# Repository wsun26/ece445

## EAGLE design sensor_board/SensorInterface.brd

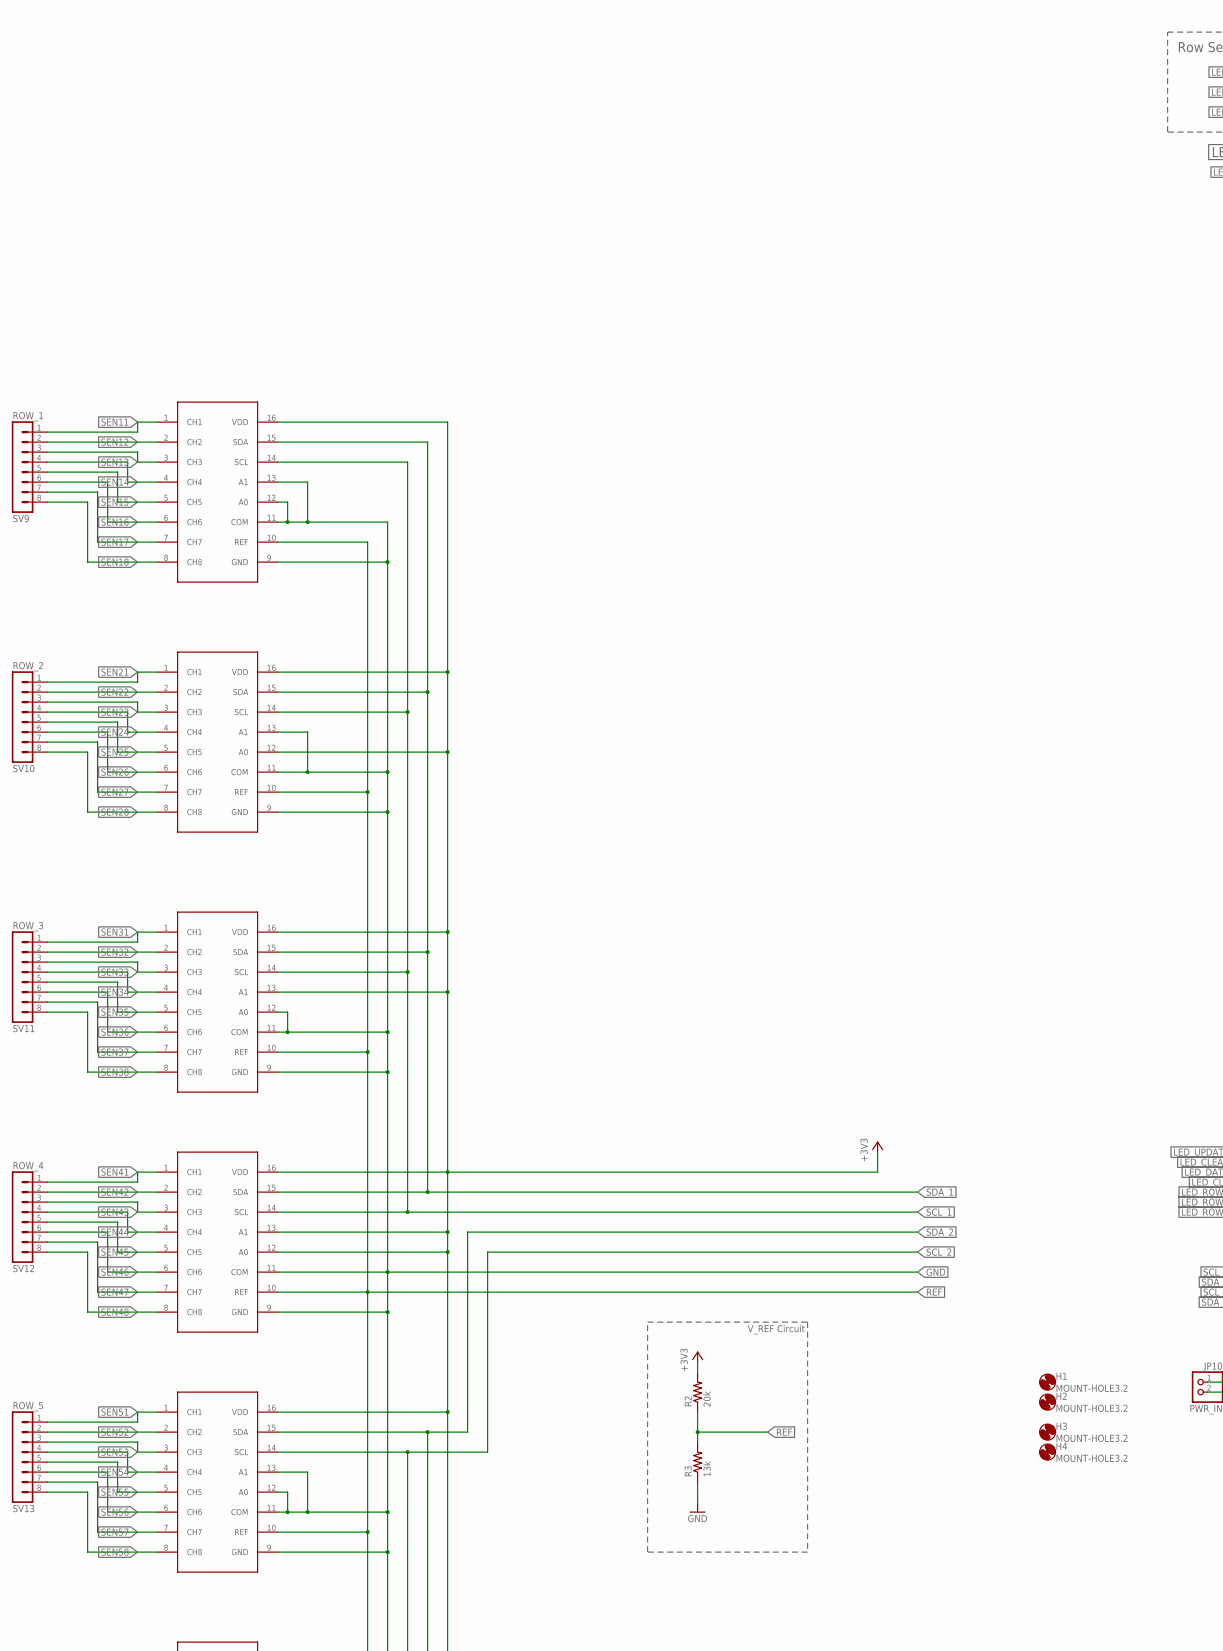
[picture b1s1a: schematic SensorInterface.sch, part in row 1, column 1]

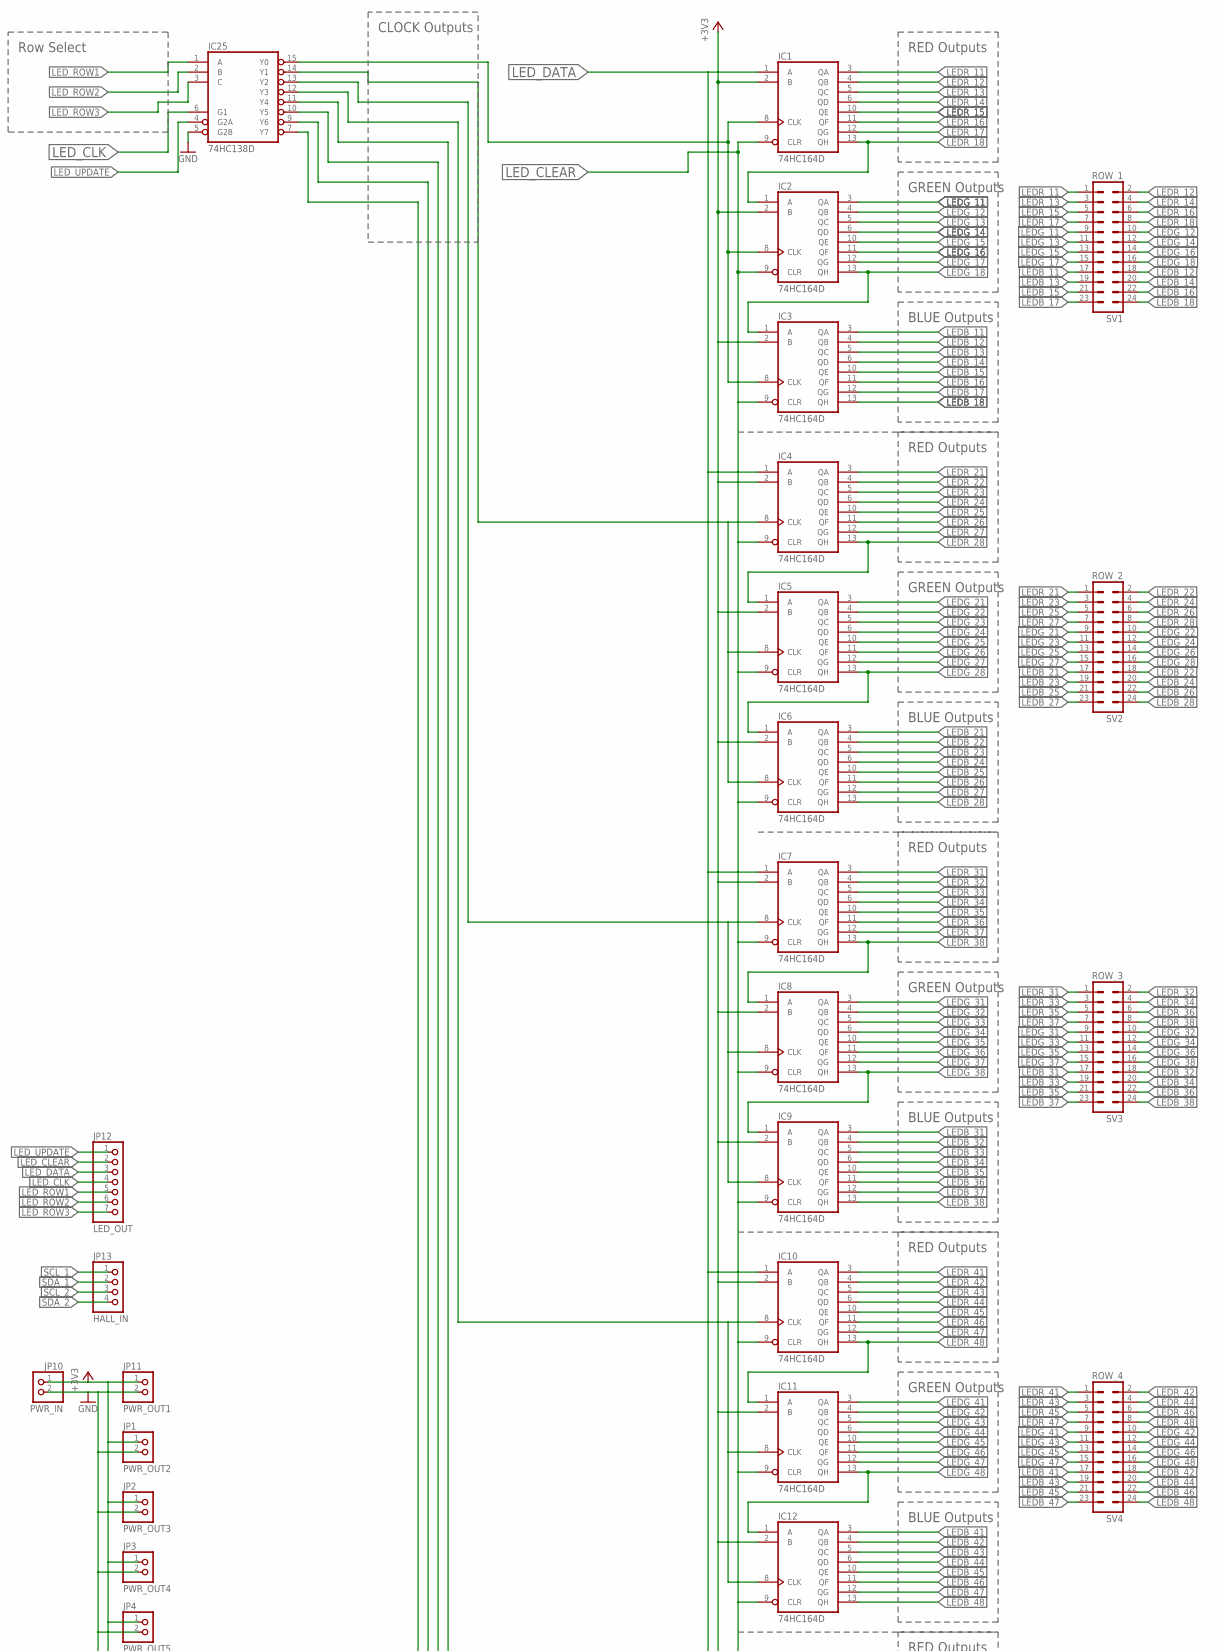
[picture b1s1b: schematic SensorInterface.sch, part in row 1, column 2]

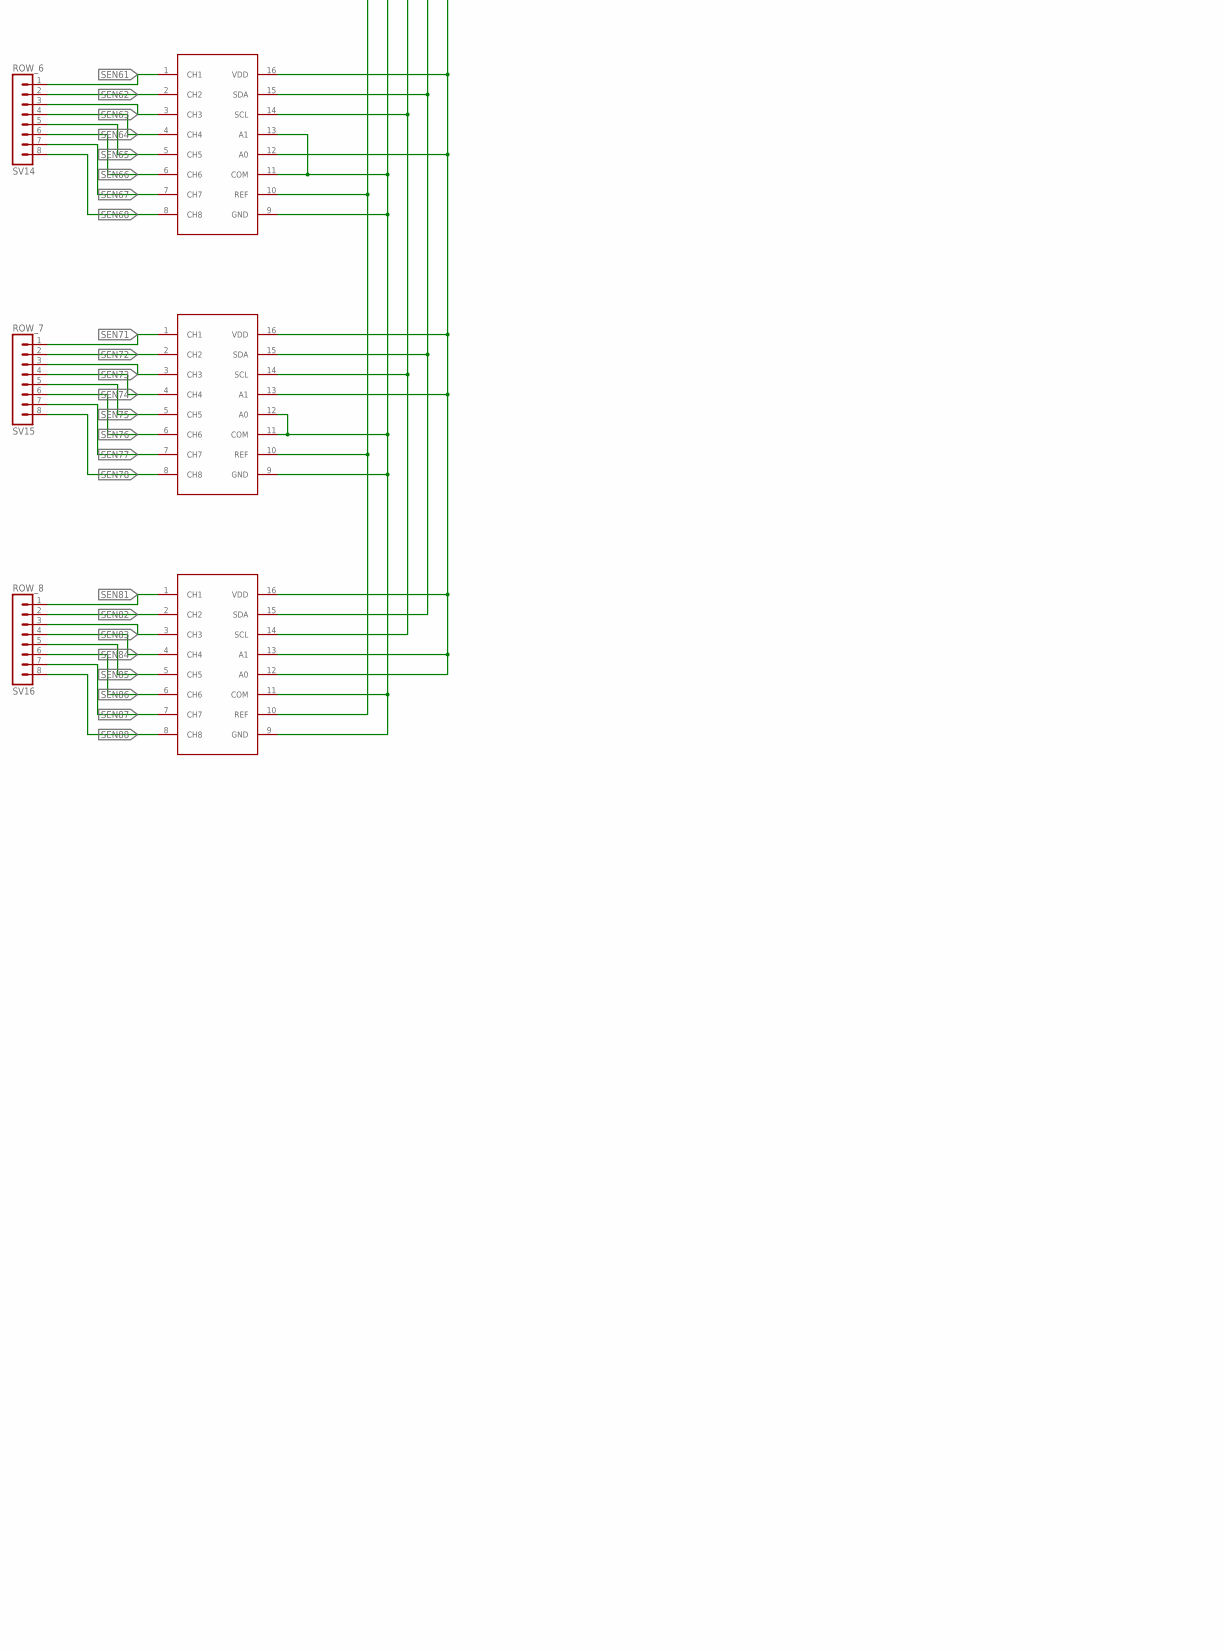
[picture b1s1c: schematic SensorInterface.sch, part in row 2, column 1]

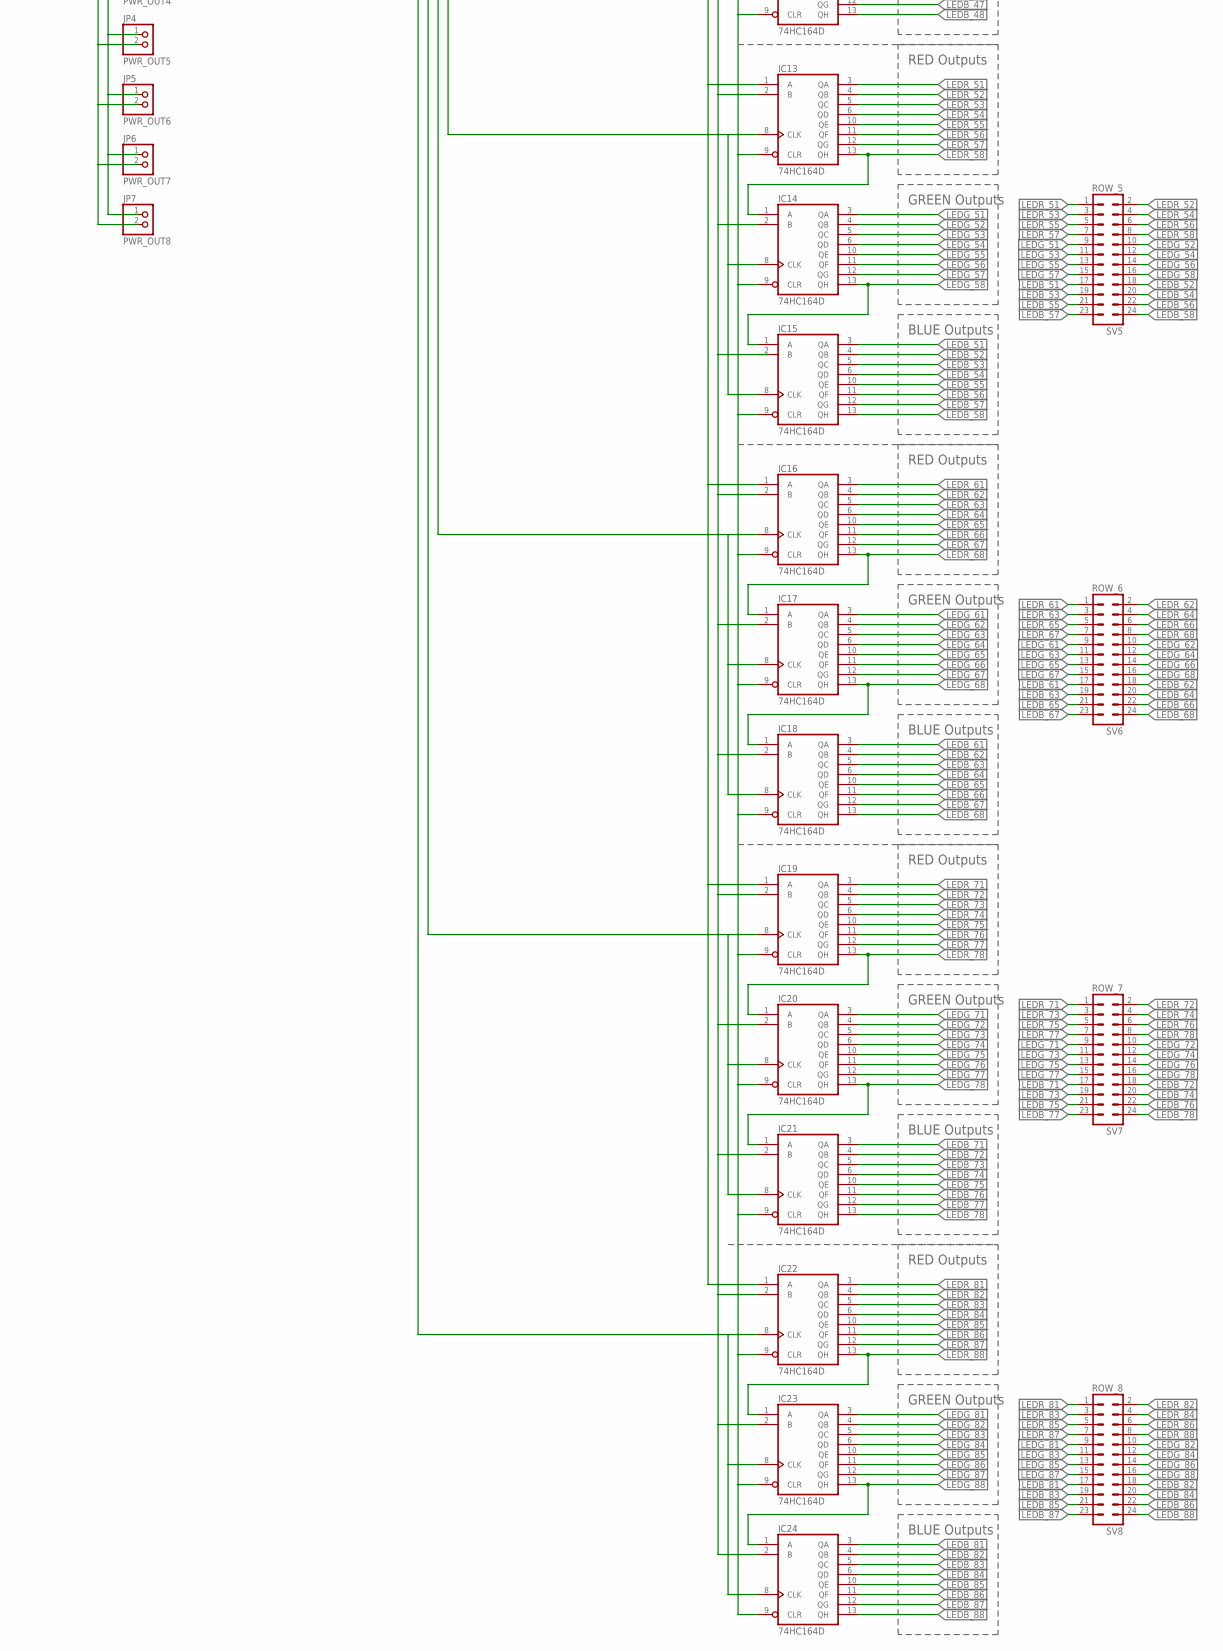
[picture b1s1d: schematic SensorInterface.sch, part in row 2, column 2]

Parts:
H1, H2, H3, H4: MOUNT-HOLE3.2; 3,2
IC1, IC2, IC3, IC4, IC5, IC6, IC7, IC8, IC9, IC10, IC11, IC12, IC13, IC14, IC15, IC16, IC17, IC18, IC19, IC20, IC21, IC22, IC23, IC24: 74HC164D; SO14
IC25: 74HC138D; SO16
JP1: PWR_OUT2; 1X02
JP2: PWR_OUT3; 1X02
JP3: PWR_OUT4; 1X02
JP4: PWR_OUT5; 1X02
JP5: PWR_OUT6; 1X02
JP6: PWR_OUT7; 1X02
JP7: PWR_OUT8; 1X02
JP10: PWR_IN; 1X02
JP11: PWR_OUT1; 1X02
JP12: LED_OUT; 1X07
JP13: HALL_IN; 1X04
R2: 20k; R0603
R3: 13k; R0603
SV1: ROW_1; MA12-2
SV2: ROW_2; MA12-2
SV3: ROW_3; MA12-2
SV4: ROW_4; MA12-2
SV5: ROW_5; MA12-2
SV6: ROW_6; MA12-2
SV7: ROW_7; MA12-2
SV8: ROW_8; MA12-2
SV9: ROW_1; MA08-1
SV10: ROW_2; MA08-1
SV11: ROW_3; MA08-1
SV12: ROW_4; MA08-1
SV13: ROW_5; MA08-1
SV14: ROW_6; MA08-1
SV15: ROW_7; MA08-1
SV16: ROW_8; MA08-1
U$1, U$2, U$3, U$4, U$5, U$6, U$7, U$8: NCD9830; TSSOP16

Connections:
+3V3: IC1.2 (B), IC2.2 (B), IC3.2 (B), IC4.2 (B), IC5.2 (B), IC6.2 (B), IC7.2 (B), IC8.2 (B), IC9.2 (B), IC10.2 (B), IC11.2 (B), IC12.2 (B), IC13.2 (B), IC14.2 (B), IC16.2 (B), IC17.2 (B), IC18.2 (B), IC19.2 (B), IC20.2 (B), IC21.2 (B), IC22.2 (B), IC23.2 (B), IC24.2 (B), JP1.1, JP2.1, JP3.1, JP4.1, JP5.1, JP6.1, JP7.1, JP10.1, JP11.1, R2.2, U$1.12 (A0), U$1.16 (VDD), U$2.13 (A1), U$2.16 (VDD), U$3.12 (A0), U$3.13 (A1), U$3.16 (VDD), U$4.16 (VDD), U$5.12 (A0), U$5.16 (VDD), U$6.13 (A1), U$6.16 (VDD), U$7.16 (VDD), U$8.12 (A0), U$8.13 (A1), U$8.16 (VDD)
CLK: IC19.8 (CLK), IC20.8 (CLK), IC21.8 (CLK), IC25.9 (Y6)
GND: IC1.7 (GND), IC2.7 (GND), IC3.7 (GND), IC4.7 (GND), IC5.7 (GND), IC6.7 (GND), IC7.7 (GND), IC8.7 (GND), IC9.7 (GND), IC10.7 (GND), IC11.7 (GND), IC12.7 (GND), IC13.7 (GND), IC14.7 (GND), IC15.7 (GND), IC16.7 (GND), IC17.7 (GND), IC18.7 (GND), IC19.7 (GND), IC20.7 (GND), IC21.7 (GND), IC22.7 (GND), IC23.7 (GND), IC24.7 (GND), IC25.5 (G2B), IC25.8 (GND), JP1.2, JP2.2, JP3.2, JP4.2, JP5.2, JP6.2, JP7.2, JP10.2, JP11.2, R3.1, U$1.9 (GND), U$1.11 (COM), U$1.13 (A1), U$2.9 (GND), U$2.11 (COM), U$2.12 (A0), U$3.9 (GND), U$3.11 (COM), U$4.9 (GND), U$4.11 (COM), U$4.12 (A0), U$4.13 (A1), U$5.9 (GND), U$5.11 (COM), U$5.13 (A1), U$6.9 (GND), U$6.11 (COM), U$6.12 (A0), U$7.9 (GND), U$7.11 (COM), U$7.12 (A0), U$7.13 (A1), U$8.9 (GND), U$8.11 (COM)
LEDB_11: IC3.3 (QA), SV1.17
LEDB_12: IC3.4 (QB), SV1.18
LEDB_13: IC3.5 (QC), SV1.19
LEDB_14: IC3.6 (QD), SV1.20
LEDB_15: IC3.10 (QE), SV1.21
LEDB_16: IC3.11 (QF), SV1.22
LEDB_17: IC3.12 (QG), SV1.23
LEDB_18: IC3.13 (QH), SV1.24
LEDB_21: IC6.3 (QA), SV2.17
LEDB_22: IC6.4 (QB), SV2.18
LEDB_23: IC6.5 (QC), SV2.19
LEDB_24: IC6.6 (QD), SV2.20
LEDB_25: IC6.10 (QE), SV2.21
LEDB_26: IC6.11 (QF), SV2.22
LEDB_27: IC6.12 (QG), SV2.23
LEDB_28: IC6.13 (QH), SV2.24
LEDB_31: IC9.3 (QA), SV3.17
LEDB_32: IC9.4 (QB), SV3.18
LEDB_33: IC9.5 (QC), SV3.19
LEDB_34: IC9.6 (QD), SV3.20
LEDB_35: IC9.10 (QE), SV3.21
LEDB_36: IC9.11 (QF), SV3.22
LEDB_37: IC9.12 (QG), SV3.23
LEDB_38: IC9.13 (QH), SV3.24
LEDB_41: IC12.3 (QA), SV4.17
LEDB_42: IC12.4 (QB), SV4.18
LEDB_43: IC12.5 (QC), SV4.19
LEDB_44: IC12.6 (QD), SV4.20
LEDB_45: IC12.10 (QE), SV4.21
LEDB_46: IC12.11 (QF), SV4.22
LEDB_47: IC12.12 (QG), SV4.23
LEDB_48: IC12.13 (QH), SV4.24
LEDB_51: IC15.3 (QA), SV5.17
LEDB_52: IC15.4 (QB), SV5.18
LEDB_53: IC15.5 (QC), SV5.19
LEDB_54: IC15.6 (QD), SV5.20
LEDB_55: IC15.10 (QE), SV5.21
LEDB_56: IC15.11 (QF), SV5.22
LEDB_57: IC15.12 (QG), SV5.23
LEDB_58: IC15.13 (QH), SV5.24
LEDB_61: IC18.3 (QA), SV6.17
LEDB_62: IC18.4 (QB), SV6.18
LEDB_63: IC18.5 (QC), SV6.19
LEDB_64: IC18.6 (QD), SV6.20
LEDB_65: IC18.10 (QE), SV6.21
LEDB_66: IC18.11 (QF), SV6.22
LEDB_67: IC18.12 (QG), SV6.23
LEDB_68: IC18.13 (QH), SV6.24
LEDB_71: IC21.3 (QA), SV7.17
LEDB_72: IC21.4 (QB), SV7.18
LEDB_73: IC21.5 (QC), SV7.19
LEDB_74: IC21.6 (QD), SV7.20
LEDB_75: IC21.10 (QE), SV7.21
LEDB_76: IC21.11 (QF), SV7.22
LEDB_77: IC21.12 (QG), SV7.23
LEDB_78: IC21.13 (QH), SV7.24
LEDB_81: IC24.3 (QA), SV8.17
LEDB_82: IC24.4 (QB), SV8.18
LEDB_83: IC24.5 (QC), SV8.19
LEDB_84: IC24.6 (QD), SV8.20
LEDB_85: IC24.10 (QE), SV8.21
LEDB_86: IC24.11 (QF), SV8.22
LEDB_87: IC24.12 (QG), SV8.23
LEDB_88: IC24.13 (QH), SV8.24
LEDG_11: IC2.3 (QA), SV1.9
LEDG_12: IC2.4 (QB), SV1.10
LEDG_13: IC2.5 (QC), SV1.11
LEDG_14: IC2.6 (QD), SV1.12
LEDG_15: IC2.10 (QE), SV1.13
LEDG_16: IC2.11 (QF), SV1.14
LEDG_17: IC2.12 (QG), SV1.15
LEDG_18: IC2.13 (QH), IC3.1 (A), SV1.16
LEDG_21: IC5.3 (QA), SV2.9
LEDG_22: IC5.4 (QB), SV2.10
LEDG_23: IC5.5 (QC), SV2.11
LEDG_24: IC5.6 (QD), SV2.12
LEDG_25: IC5.10 (QE), SV2.13
LEDG_26: IC5.11 (QF), SV2.14
LEDG_27: IC5.12 (QG), SV2.15
LEDG_28: IC5.13 (QH), IC6.1 (A), SV2.16
LEDG_31: IC8.3 (QA), SV3.9
LEDG_32: IC8.4 (QB), SV3.10
LEDG_33: IC8.5 (QC), SV3.11
LEDG_34: IC8.6 (QD), SV3.12
LEDG_35: IC8.10 (QE), SV3.13
LEDG_36: IC8.11 (QF), SV3.14
LEDG_37: IC8.12 (QG), SV3.15
LEDG_38: IC8.13 (QH), IC9.1 (A), SV3.16
LEDG_41: IC11.3 (QA), SV4.9
LEDG_42: IC11.4 (QB), SV4.10
LEDG_43: IC11.5 (QC), SV4.11
LEDG_44: IC11.6 (QD), SV4.12
LEDG_45: IC11.10 (QE), SV4.13
LEDG_46: IC11.11 (QF), SV4.14
LEDG_47: IC11.12 (QG), SV4.15
LEDG_48: IC11.13 (QH), IC12.1 (A), SV4.16
LEDG_51: IC14.3 (QA), SV5.9
LEDG_52: IC14.4 (QB), SV5.10
LEDG_53: IC14.5 (QC), SV5.11
LEDG_54: IC14.6 (QD), SV5.12
LEDG_55: IC14.10 (QE), SV5.13
LEDG_56: IC14.11 (QF), SV5.14
LEDG_57: IC14.12 (QG), SV5.15
LEDG_58: IC14.13 (QH), IC15.1 (A), SV5.16
LEDG_61: IC17.3 (QA), SV6.9
LEDG_62: IC17.4 (QB), SV6.10
LEDG_63: IC17.5 (QC), SV6.11
LEDG_64: IC17.6 (QD), SV6.12
LEDG_65: IC17.10 (QE), SV6.13
LEDG_66: IC17.11 (QF), SV6.14
LEDG_67: IC17.12 (QG), SV6.15
LEDG_68: IC17.13 (QH), IC18.1 (A), SV6.16
LEDG_71: IC20.3 (QA), SV7.9
LEDG_72: IC20.4 (QB), SV7.10
LEDG_73: IC20.5 (QC), SV7.11
LEDG_74: IC20.6 (QD), SV7.12
LEDG_75: IC20.10 (QE), SV7.13
LEDG_76: IC20.11 (QF), SV7.14
LEDG_77: IC20.12 (QG), SV7.15
LEDG_78: IC20.13 (QH), IC21.1 (A), SV7.16
LEDG_81: IC23.3 (QA), SV8.9
LEDG_82: IC23.4 (QB), SV8.10
LEDG_83: IC23.5 (QC), SV8.11
LEDG_84: IC23.6 (QD), SV8.12
LEDG_85: IC23.10 (QE), SV8.13
LEDG_86: IC23.11 (QF), SV8.14
LEDG_87: IC23.12 (QG), SV8.15
LEDG_88: IC23.13 (QH), IC24.1 (A), SV8.16
LEDR_11: IC1.3 (QA), SV1.1
LEDR_12: IC1.4 (QB), SV1.2
LEDR_13: IC1.5 (QC), SV1.3
LEDR_14: IC1.6 (QD), SV1.4
LEDR_15: IC1.10 (QE), SV1.5
LEDR_16: IC1.11 (QF), SV1.6
LEDR_17: IC1.12 (QG), SV1.7
LEDR_18: IC1.13 (QH), IC2.1 (A), SV1.8
LEDR_21: IC4.3 (QA), SV2.1
LEDR_22: IC4.4 (QB), SV2.2
LEDR_23: IC4.5 (QC), SV2.3
LEDR_24: IC4.6 (QD), SV2.4
LEDR_25: IC4.10 (QE), SV2.5
LEDR_26: IC4.11 (QF), SV2.6
LEDR_27: IC4.12 (QG), SV2.7
LEDR_28: IC4.13 (QH), IC5.1 (A), SV2.8
LEDR_31: IC7.3 (QA), SV3.1
LEDR_32: IC7.4 (QB), SV3.2
LEDR_33: IC7.5 (QC), SV3.3
LEDR_34: IC7.6 (QD), SV3.4
LEDR_35: IC7.10 (QE), SV3.5
LEDR_36: IC7.11 (QF), SV3.6
LEDR_37: IC7.12 (QG), SV3.7
LEDR_38: IC7.13 (QH), IC8.1 (A), SV3.8
LEDR_41: IC10.3 (QA), SV4.1
LEDR_42: IC10.4 (QB), SV4.2
LEDR_43: IC10.5 (QC), SV4.3
LEDR_44: IC10.6 (QD), SV4.4
LEDR_45: IC10.10 (QE), SV4.5
LEDR_46: IC10.11 (QF), SV4.6
LEDR_47: IC10.12 (QG), SV4.7
LEDR_48: IC10.13 (QH), IC11.1 (A), SV4.8
LEDR_51: IC13.3 (QA), SV5.1
LEDR_52: IC13.4 (QB), SV5.2
LEDR_53: IC13.5 (QC), SV5.3
LEDR_54: IC13.6 (QD), SV5.4
LEDR_55: IC13.10 (QE), SV5.5
LEDR_56: IC13.11 (QF), SV5.6
LEDR_57: IC13.12 (QG), SV5.7
LEDR_58: IC13.13 (QH), IC14.1 (A), SV5.8
LEDR_61: IC16.3 (QA), SV6.1
LEDR_62: IC16.4 (QB), SV6.2
LEDR_63: IC16.5 (QC), SV6.3
LEDR_64: IC16.6 (QD), SV6.4
LEDR_65: IC16.10 (QE), SV6.5
LEDR_66: IC16.11 (QF), SV6.6
LEDR_67: IC16.12 (QG), SV6.7
LEDR_68: IC16.13 (QH), IC17.1 (A), SV6.8
LEDR_71: IC19.3 (QA), SV7.1
LEDR_72: IC19.4 (QB), SV7.2
LEDR_73: IC19.5 (QC), SV7.3
LEDR_74: IC19.6 (QD), SV7.4
LEDR_75: IC19.10 (QE), SV7.5
LEDR_76: IC19.11 (QF), SV7.6
LEDR_77: IC19.12 (QG), SV7.7
LEDR_78: IC19.13 (QH), IC20.1 (A), SV7.8
LEDR_81: IC22.3 (QA), SV8.1
LEDR_82: IC22.4 (QB), SV8.2
LEDR_83: IC22.5 (QC), SV8.3
LEDR_84: IC22.6 (QD), SV8.4
LEDR_85: IC22.10 (QE), SV8.5
LEDR_86: IC22.11 (QF), SV8.6
LEDR_87: IC22.12 (QG), SV8.7
LEDR_88: IC22.13 (QH), IC23.1 (A), SV8.8
LED_CLEAR: IC1.9 (CLR), IC2.9 (CLR), IC3.9 (CLR), IC4.9 (CLR), IC5.9 (CLR), IC6.9 (CLR), IC7.9 (CLR), IC8.9 (CLR), IC9.9 (CLR), IC10.9 (CLR), IC11.9 (CLR), IC12.9 (CLR), IC13.9 (CLR), IC14.9 (CLR), IC15.9 (CLR), IC16.9 (CLR), IC17.9 (CLR), IC18.9 (CLR), IC19.9 (CLR), IC20.9 (CLR), IC21.9 (CLR), IC22.9 (CLR), IC23.9 (CLR), IC24.9 (CLR), JP12.2
LED_CLK: IC25.6 (G1), JP12.4
LED_DATA: IC1.1 (A), IC4.1 (A), IC7.1 (A), IC10.1 (A), IC13.1 (A), IC16.1 (A), IC19.1 (A), IC22.1 (A), JP12.3
LED_ROW1: IC25.1 (A), JP12.5
LED_ROW2: IC25.2 (B), JP12.6
LED_ROW3: IC25.3 (C), JP12.7
LED_UPDATE: IC25.4 (G2A), JP12.1
unnamed: IC1.8 (CLK), IC2.8 (CLK), IC3.8 (CLK), IC25.15 (Y0)
unnamed: IC4.8 (CLK), IC5.8 (CLK), IC6.8 (CLK), IC25.14 (Y1)
unnamed: IC7.8 (CLK), IC8.8 (CLK), IC9.8 (CLK), IC25.13 (Y2)
unnamed: IC10.8 (CLK), IC11.8 (CLK), IC12.8 (CLK), IC25.12 (Y3)
unnamed: IC13.8 (CLK), IC14.8 (CLK), IC15.8 (CLK), IC25.11 (Y4)
unnamed: IC16.8 (CLK), IC17.8 (CLK), IC18.8 (CLK), IC25.10 (Y5)
unnamed: IC22.8 (CLK), IC23.8 (CLK), IC24.8 (CLK), IC25.7 (Y7)
REF: R2.1, R3.2, U$1.10 (REF), U$2.10 (REF), U$3.10 (REF), U$4.10 (REF), U$5.10 (REF), U$6.10 (REF), U$7.10 (REF), U$8.10 (REF)
SCL_1: JP13.1, U$1.14 (SCL), U$2.14 (SCL), U$3.14 (SCL), U$7.14 (SCL)
SCL_2: JP13.3, U$4.14 (SCL), U$5.14 (SCL), U$6.14 (SCL), U$8.14 (SCL)
SDA_1: JP13.2, U$1.15 (SDA), U$2.15 (SDA), U$3.15 (SDA), U$7.15 (SDA)
SDA_2: JP13.4, U$4.15 (SDA), U$5.15 (SDA), U$6.15 (SDA), U$8.15 (SDA)
SEN11: SV9.1, U$7.1 (CH1)
SEN12: SV9.2, U$7.2 (CH2)
SEN13: SV9.3, U$7.3 (CH3)
SEN14: SV9.4, U$7.4 (CH4)
SEN15: SV9.5, U$7.5 (CH5)
SEN16: SV9.6, U$7.6 (CH6)
SEN17: SV9.7, U$7.7 (CH7)
SEN18: SV9.8, U$7.8 (CH8)
SEN21: SV10.1
SEN22: SV10.2
SEN23: SV10.3
SEN24: SV10.4
SEN25: SV10.5
SEN26: SV10.6
SEN27: SV10.7
SEN28: SV10.8
SEN31: SV11.1
SEN32: SV11.2
SEN33: SV11.3
SEN34: SV11.4
SEN35: SV11.5
SEN36: SV11.6
SEN37: SV11.7
SEN38: SV11.8
SEN41: SV12.1
SEN42: SV12.2
SEN43: SV12.3
SEN44: SV12.4
SEN45: SV12.5
SEN46: SV12.6
SEN47: SV12.7
SEN48: SV12.8
SEN51: SV13.1
SEN52: SV13.2
SEN53: SV13.3
SEN54: SV13.4
SEN55: SV13.5
SEN56: SV13.6
SEN57: SV13.7
SEN58: SV13.8
SEN61: SV14.1
SEN62: SV14.2
SEN63: SV14.3
SEN64: SV14.4
SEN65: SV14.5
SEN66: SV14.6
SEN67: SV14.7
SEN68: SV14.8
SEN71: SV15.1
SEN72: SV15.2
SEN73: SV15.3
SEN74: SV15.4
SEN75: SV15.5
SEN76: SV15.6
SEN77: SV15.7
SEN78: SV15.8
SEN81: SV16.1
SEN82: SV16.2
SEN83: SV16.3
SEN84: SV16.4
SEN85: SV16.5
SEN86: SV16.6
SEN87: SV16.7
SEN88: SV16.8
VCC: IC1.14 (VCC), IC2.14 (VCC), IC3.14 (VCC), IC4.14 (VCC), IC5.14 (VCC), IC6.14 (VCC), IC7.14 (VCC), IC8.14 (VCC), IC9.14 (VCC), IC10.14 (VCC), IC11.14 (VCC), IC12.14 (VCC), IC13.14 (VCC), IC14.14 (VCC), IC15.14 (VCC), IC16.14 (VCC), IC17.14 (VCC), IC18.14 (VCC), IC19.14 (VCC), IC20.14 (VCC), IC21.14 (VCC), IC22.14 (VCC), IC23.14 (VCC), IC24.14 (VCC), IC25.16 (VCC)

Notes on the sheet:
V_REF Circuit
RED Outputs
GREEN Outputs
BLUE Outputs
CLOCK Outputs
Row Select

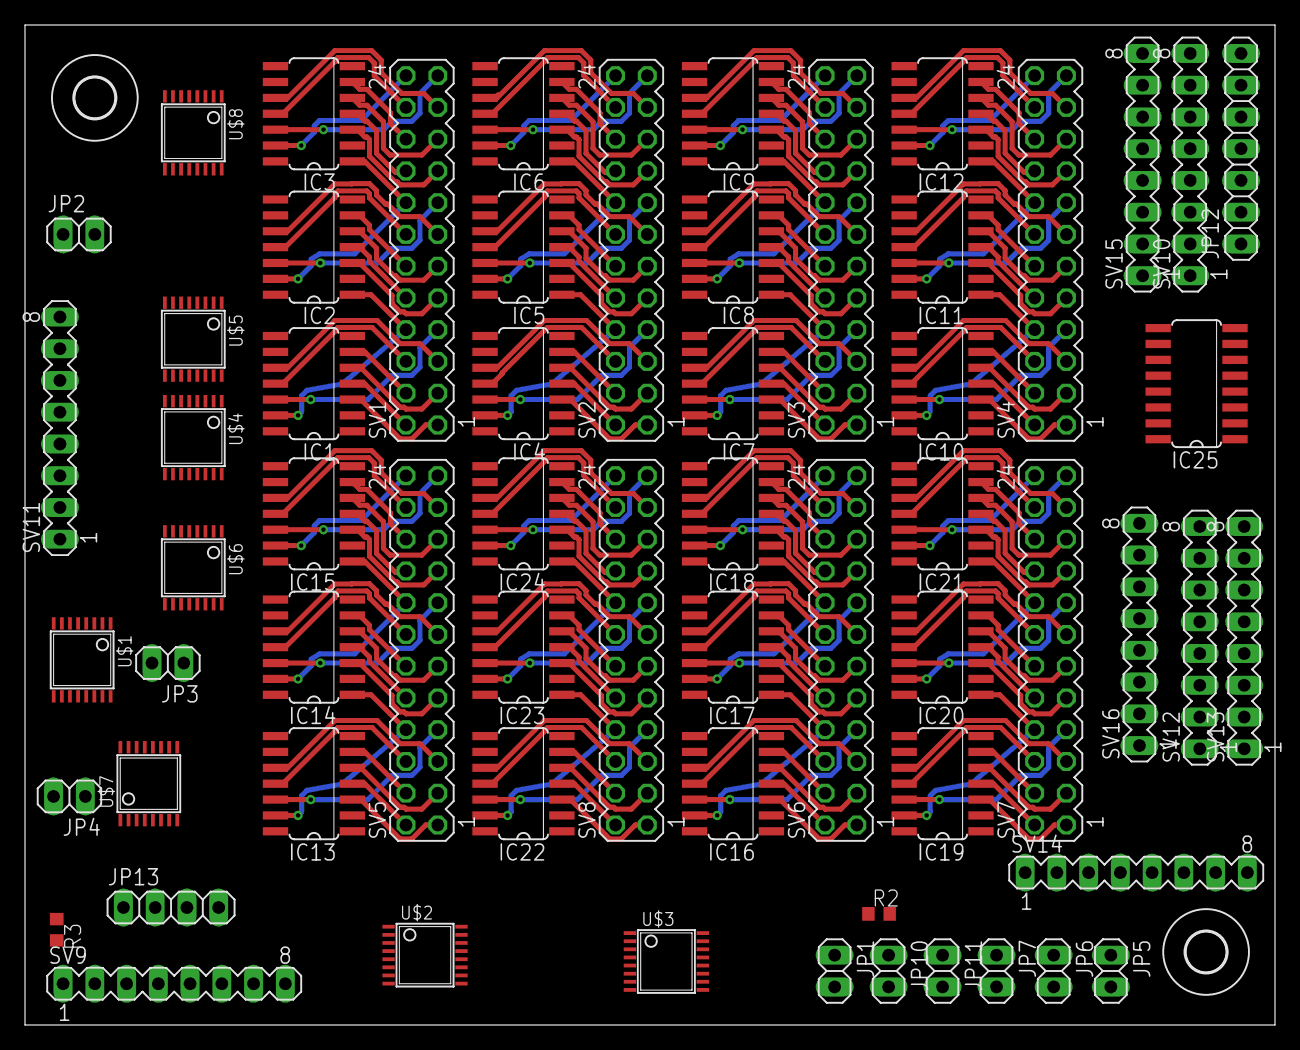
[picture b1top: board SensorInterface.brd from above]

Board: 2 copper layers, 100.0 x 80.0 mm, 66 parts (0 on the bottom side), 223 nets.

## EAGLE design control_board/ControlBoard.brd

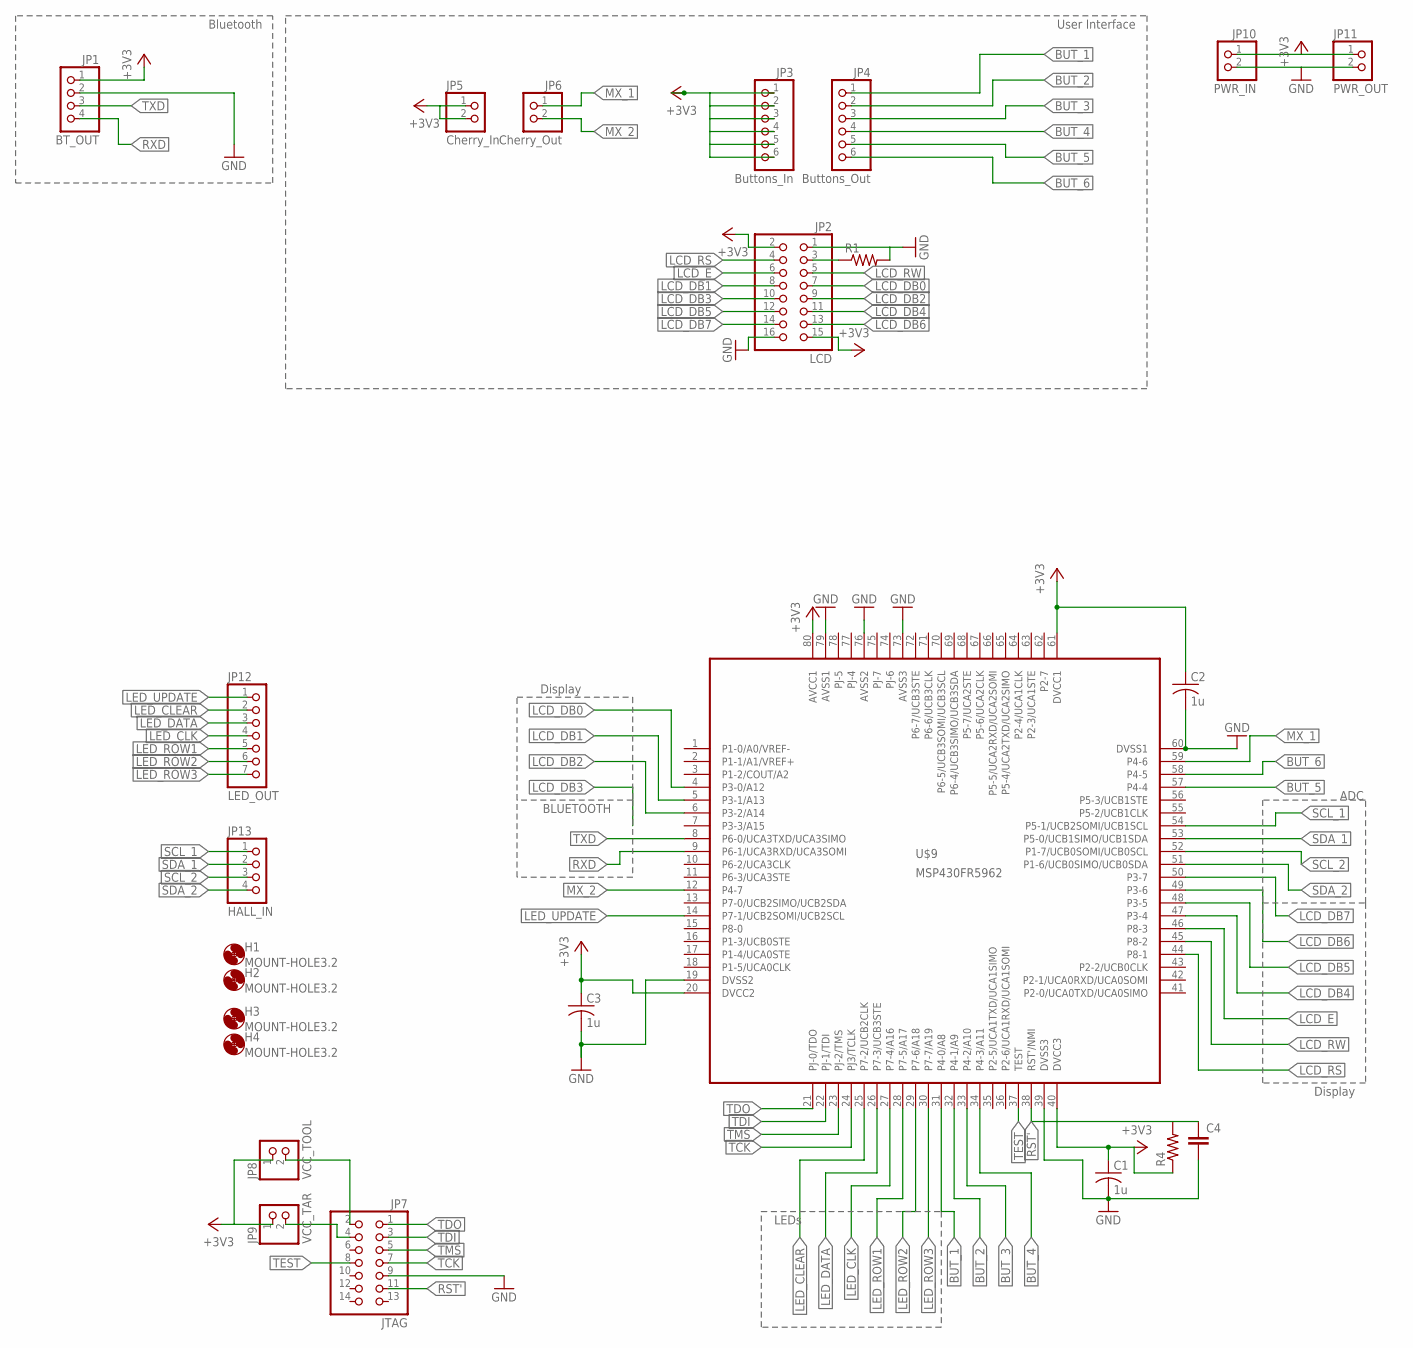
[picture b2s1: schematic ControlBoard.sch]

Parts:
C1, C2, C3: 1u; C0603
C4: C-EU025-025X050; C025-025X050
H1, H2, H3, H4: MOUNT-HOLE3.2; 3,2
JP1: BT_OUT; 1X04
JP2: LCD; 2X08
JP3: Buttons_In; 1X06
JP4: Buttons_Out; 1X06
JP5: Cherry_In; 1X02
JP6: Cherry_Out; 1X02
JP7: JTAG; 2X07
JP8: VCC_TOOL; 1X02
JP9: VCC_TAR; 1X02
JP10: PWR_IN; 1X02
JP11: PWR_OUT; 1X02
JP12: LED_OUT; 1X07
JP13: HALL_IN; 1X04
R1, R4: R-US_VMTA55; VMTA55
U$9: MSP430FR5962; LQFP80

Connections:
+3V3: C1.1, C2.1, C3.1, JP1.1, JP2.2, JP2.15, JP3.1, JP3.2, JP3.3, JP3.4, JP3.5, JP3.6, JP5.1, JP5.2, JP8.1, JP9.1, JP10.1, JP11.1, R4.1, U$9.20 (DVCC2), U$9.40 (DVCC3), U$9.61 (DVCC1), U$9.80 (AVCC1)
BUT_1: JP4.1, U$9.31 (P4-0/A8)
BUT_2: JP4.2, U$9.32 (P4-1/A9)
BUT_3: JP4.3, U$9.33 (P4-2/A10)
BUT_4: JP4.4, U$9.34 (P4-3/A11)
BUT_5: JP4.5, U$9.57 (P4-4)
BUT_6: JP4.6, U$9.58 (P4-5)
GND: C1.2, C2.2, C3.2, C4.2, JP1.2, JP2.1, JP2.16, JP7.9, JP10.2, JP11.2, R1.2, U$9.19 (DVSS2), U$9.39 (DVSS3), U$9.60 (DVSS1), U$9.73 (AVSS3), U$9.76 (AVSS2), U$9.79 (AVSS1)
LCD_DB0: JP2.7, U$9.4 (P3-0/A12)
LCD_DB1: JP2.8, U$9.5 (P3-1/A13)
LCD_DB2: JP2.9, U$9.6 (P3-2/A14)
LCD_DB3: JP2.10
LCD_DB4: JP2.11, U$9.47 (P3-4)
LCD_DB5: JP2.12, U$9.48 (P3-5)
LCD_DB6: JP2.13, U$9.49 (P3-6)
LCD_DB7: JP2.14, U$9.50 (P3-7)
LCD_E: JP2.6, U$9.46 (P8-3)
LCD_RS: JP2.4, U$9.44 (P8-1)
LCD_RW: JP2.5, U$9.45 (P8-2)
LED_CLEAR: JP12.2, U$9.25 (P7-2/UCB2CLK)
LED_CLK: JP12.4, U$9.27 (P7-4/A16)
LED_DATA: JP12.3, U$9.26 (P7-3/UCB3STE)
LED_ROW1: JP12.5, U$9.28 (P7-5/A17)
LED_ROW2: JP12.6, U$9.29 (P7-6/A18)
LED_ROW3: JP12.7, U$9.30 (P7-7/A19)
LED_UPDATE: JP12.1, U$9.14 (P7-1/UCB2SOMI/UCB2SCL)
MX_1: JP6.1, U$9.59 (P4-6)
MX_2: JP6.2, U$9.12 (P4-7)
unnamed: JP2.3, R1.1
unnamed: JP7.2, JP8.2
unnamed: JP7.4, JP9.2
P1-0/A0/VREF-: U$9.1 (P1-0/A0/VREF-)
PJ-5: U$9.78 (PJ-5)
RST': C4.1, JP7.11, R4.2, U$9.38 (RST'/NMI)
RXD: JP1.4, U$9.9 (P6-1/UCA3RXD/UCA3SOMI)
SCL_1: JP13.1, U$9.54 (P5-1/UCB2SOMI/UCB1SCL)
SCL_2: JP13.3, U$9.52 (P1-7/UCB0SOMI/UCB0SCL)
SDA_1: JP13.2, U$9.53 (P5-0/UCB1SIMO/UCB1SDA)
SDA_2: JP13.4, U$9.51 (P1-6/UCB0SIMO/UCB0SDA)
TCK: JP7.7, U$9.24 (PJ3/TCLK)
TDI: JP7.3, U$9.22 (PJ-1/TDI)
TDO: JP7.1, U$9.21 (PJ-0/TDO)
TEST: JP7.8, U$9.37 (TEST)
TMS: JP7.5, U$9.23 (PJ-2/TMS)
TXD: JP1.3, U$9.8 (P6-0/UCA3TXD/UCA3SIMO)

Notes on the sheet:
Bluetooth
User Interface
BLUETOOTH
ADC
Display
LEDs

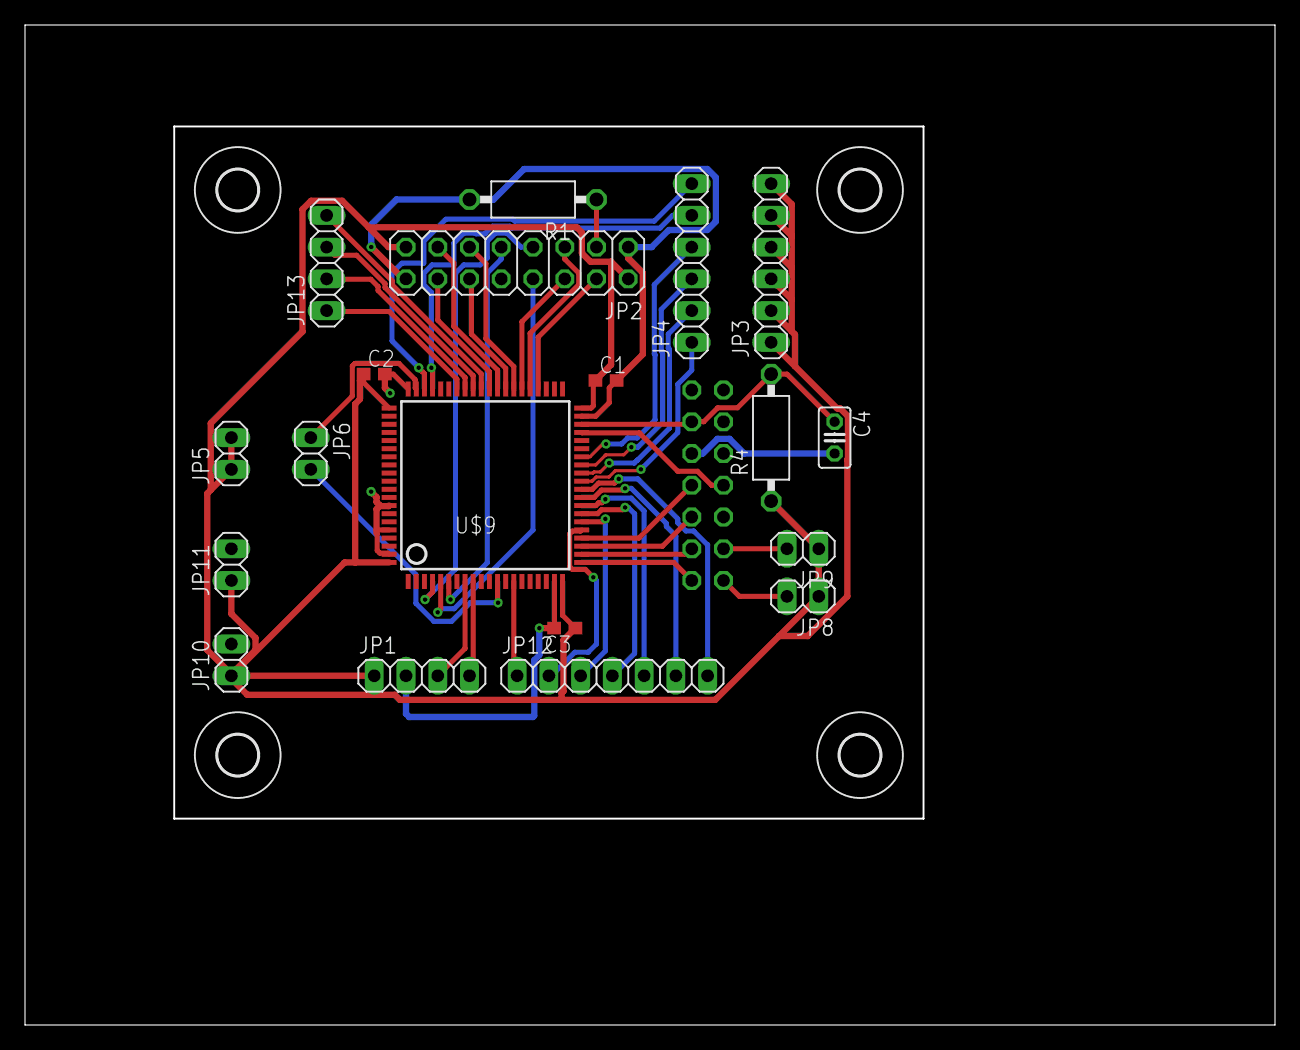
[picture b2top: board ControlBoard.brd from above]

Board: 2 copper layers, 99.8 x 79.8 mm, 24 parts (1 on the bottom side), 42 nets.

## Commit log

2019-05-03 445_init
